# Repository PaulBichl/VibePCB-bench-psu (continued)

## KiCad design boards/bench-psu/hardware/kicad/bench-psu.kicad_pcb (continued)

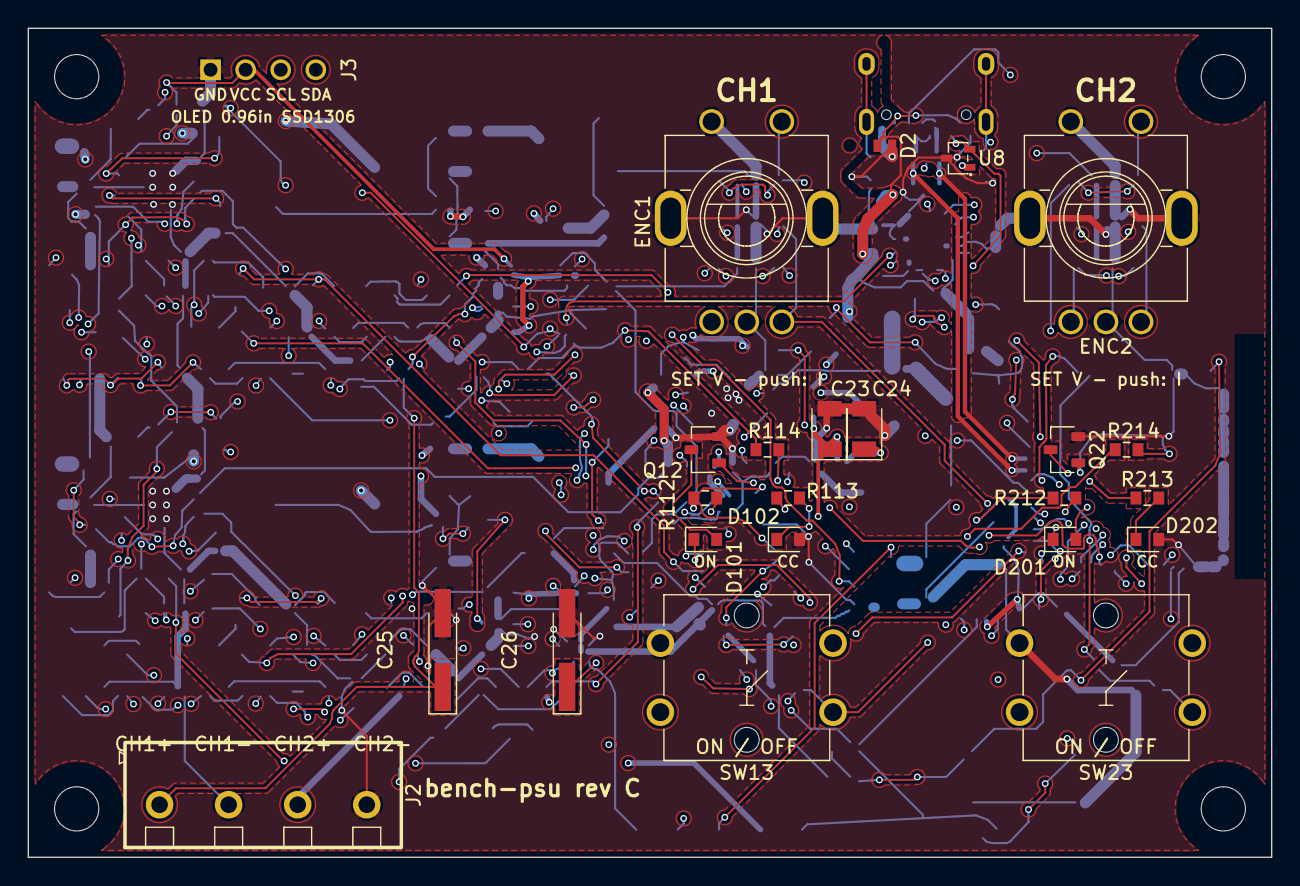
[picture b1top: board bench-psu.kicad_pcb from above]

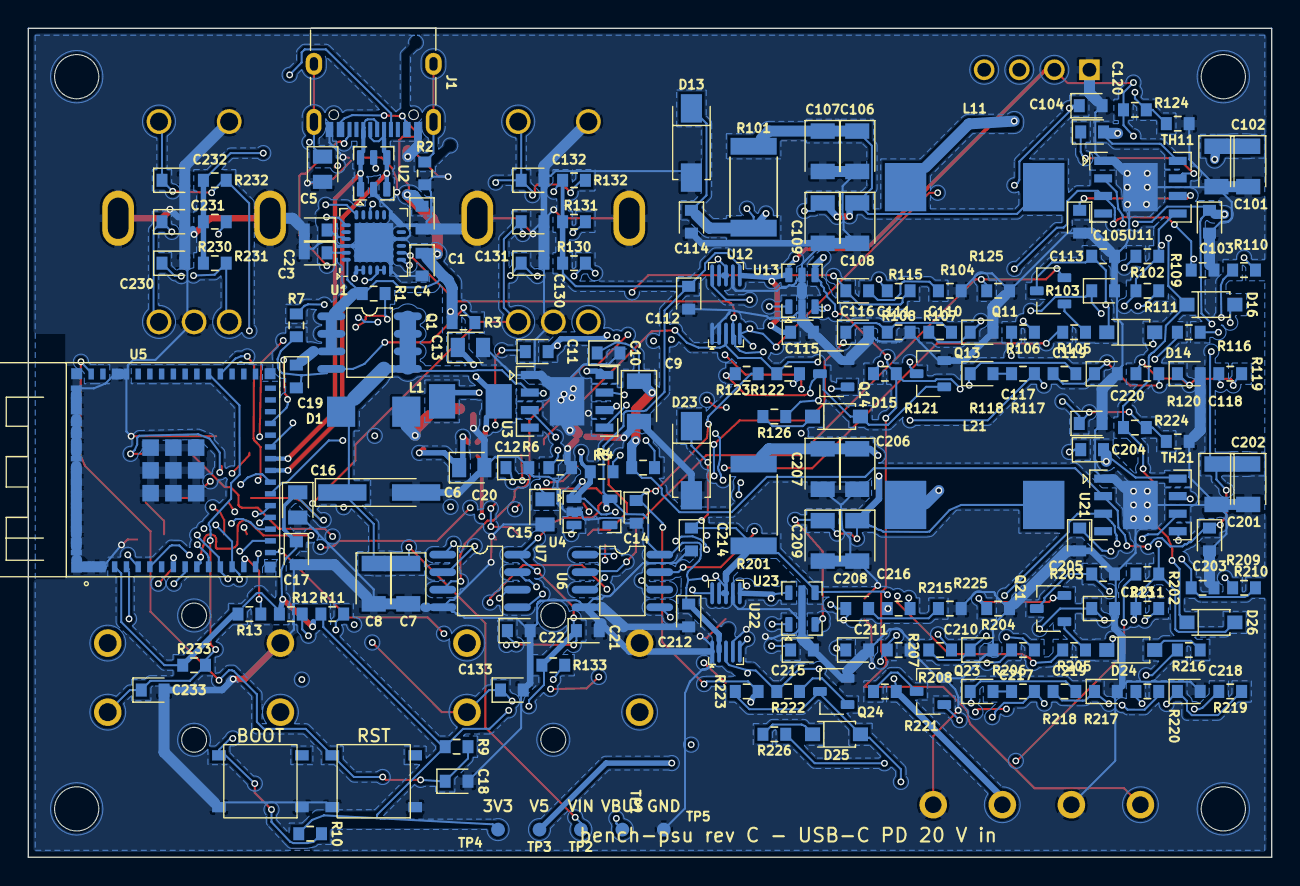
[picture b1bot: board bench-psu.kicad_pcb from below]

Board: 4 copper layers, 90.0 x 60.0 mm, 202 parts (178 on the bottom side), 103 nets.

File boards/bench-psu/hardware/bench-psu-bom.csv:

"Qty","Designator","Value","Footprint","MPN","LCSC Part #"
"14","C1,C2,C3,C14,C18,C20,C105,C110,C111,C118,C205,C210,C211,C218","1uF","tscircuit:capacitor_cap0603","","C15849"
"22","C4,C11,C17,C19,C21,C22,C104,C112,C114,C115,C116,C117,C119,C120,C204,C212,C214,C215,C216,C217,C219,C220","100nF","tscircuit:capacitor_cap0603","","C14663"
"1","C5","4.7nF","tscircuit:capacitor_cap0805","","C565695"
"3","C6,C25,C26","100uF","tscircuit:RVT1V101M0607_100UF_35V","RVT1V101M0607 100UF 35V","C970686"
"7","C7,C8,C9,C101,C102,C201,C202","10uF","tscircuit:capacitor_cap1206","","C13585"
"3","C10,C103,C203","220nF","tscircuit:capacitor_cap0603","","C107083"
"2","C12,C13","22uF","tscircuit:capacitor_cap0805","","C45783"
"2","C15,C16","10uF","tscircuit:capacitor_cap0805","","C15850"
"10","C23,C24,C106,C107,C108,C109,C206,C207,C208,C209","22uF","tscircuit:capacitor_cap1206","","C12891"
"2","C113,C213","220nF","tscircuit:capacitor_cap0603","","C21120"
"8","C130,C131,C132,C133,C230,C231,C232,C233","33nF","tscircuit:capacitor_cap0603","","C21117"
"1","D1","SMBJ22A","tscircuit:SMBJ22A","SMBJ22A","C151920"
"1","D2","ESDA25P35-1U1M","tscircuit:ESDA25P35-1U1M","ESDA25P35-1U1M","C1974707"
"2","D13,D23","SS54","tscircuit:SS54","SS54","C22452"
"6","D14,D15,D16,D24,D25,D26","1N4148W","tscircuit:1N4148W","1N4148W","C81598"
"2","D101,D201","KT-0603YG","tscircuit:KT-0603YG","KT-0603YG","C2289"
"2","D102,D202","KT-0603R","tscircuit:KT-0603R","KT-0603R","C2286"
"2","ENC1,ENC2","EC11E15244B2","tscircuit:EC11E15244B2","EC11E15244B2","C470754"
"1","J1","TYPE-C 16PIN 2MD(073)","tscircuit:TYPE-C_16PIN_2MD_073","TYPE-C 16PIN 2MD(073)","C2765186"
"1","J2","DG301-5.0-04P-14-1000A(H)","tscircuit:DG301-5_0-04P-14-1000A_H","DG301-5.0-04P-14-1000A(H)","C3037697"
"1","J3","PZ254V-11-04P","tscircuit:PZ254V-11-04P","PZ254V-11-04P","C492403"
"1","L1","6.8µH","tscircuit:FXL0530-6R8-M","FXL0530-6R8-M","C177249"
"2","L11,L21","15µH","tscircuit:FXL1040-150-M","FXL1040-150-M","C475916"
"1","Q1","AO4407A","tscircuit:AO4407A","AO4407A","C2841482"
"6","Q11,Q12,Q14,Q21,Q22,Q24","MMBT3904(RANGE:100-300)","tscircuit:MMBT3904_RANGE_100-300","MMBT3904(RANGE:100-300)","C20526"
"2","Q13,Q23","2N7002","tscircuit:2N7002","2N7002","C8545"
"7","R1,R105,R112,R113,R205,R212,R213","1kΩ","tscircuit:resistor_res0603","","C21190"
"1","R2","1MΩ","tscircuit:resistor_res0603","","C22935"
"11","R3,R4,R5,R107,R109,R120,R126,R207,R209,R220,R226","100kΩ","tscircuit:resistor_res0603","","C25803"
"1","R6","24kΩ","tscircuit:resistor_res0603","","C23352"
"7","R7,R114,R122,R123,R214,R222,R223","47kΩ","tscircuit:resistor_res0603","","C25819"
"19","R9,R10,R13,R106,R108,R110,R115,R116,R117,R119,R124,R206,R208,R210,R215,R216,R217,R219,R224","10kΩ","tscircuit:resistor_res0603","","C25804"
"4","R11,R12,R121,R221","4.7kΩ","tscircuit:resistor_res0603","","C23162"
"2","R101,R201","20mΩ","tscircuit:resistor_res2512","","C105360"
"2","R102,R202","120kΩ","tscircuit:resistor_res0603","","C25808"
"2","R103,R203","200kΩ","tscircuit:resistor_res0603","","C25811"
"2","R104,R204","2.2kΩ","tscircuit:resistor_res0603","","C4190"
"2","R111,R211","6.8kΩ","tscircuit:resistor_res0603","","C23212"
"4","R118,R125,R218,R225","330Ω","tscircuit:resistor_res0603","","C23138"
"8","R130,R131,R132,R133,R230,R231,R232,R233","3.3kΩ","tscircuit:resistor_res0603","","C22978"
"2","SW1,SW2","TS-1187A-B-A-B","tscircuit:TS-1187A-B-A-B","TS-1187A-B-A-B","C318884"
"2","SW13,SW23","B3F-4055","tscircuit:B3F-4055","B3F-4055","C84931"
"2","TH11,TH21","10kΩ","tscircuit:NCP18XH103F03RB","NCP18XH103F03RB","C13564"
"1","U1","STUSB4500QTR","tscircuit:STUSB4500QTR","STUSB4500QTR","C2678061"
"1","U2","USBLC6-2SC6","tscircuit:USBLC6-2SC6","USBLC6-2SC6","C2687116"
"3","U3,U11,U21","LMR33630ADDAR","tscircuit:LMR33630ADDAR","LMR33630ADDAR","C841384"
"1","U4","AP2112K-3.3TRG1","tscircuit:AP2112K-3_3TRG1","AP2112K-3.3TRG1","C51118"
"1","U5","ESP32-S3-MINI-1-N8","tscircuit:ESP32-S3-MINI-1-N8","ESP32-S3-MINI-1-N8","C2913206"
"2","U6,U7","TLV9062IDR","tscircuit:TLV9062IDR","TLV9062IDR","C398355"
"1","U8","ESDA25W","tscircuit:ESDA25W","ESDA25W","C2935152"
"2","U12,U22","INA226AIDGSR","tscircuit:INA226AIDGSR","INA226AIDGSR","C49851"
"2","U13,U23","INA181A2IDBVR","tscircuit:INA181A2IDBVR","INA181A2IDBVR","C2058784"
